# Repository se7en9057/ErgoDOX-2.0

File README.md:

# ErgoDOX-2.0
 
(Circuit design based on the Let's Split PCB)<br />
An update to a classic. <br />
-more switch compatibility<br />
  -MX Alps PG1350<br />
-in switch LED's<br />
-underglow RGB<br />
-Pro Micro each side for individual hand operation<br />
-same PCB layout to ensure compatibility with existing cases. <br />
  -after some consideration in order to bring this board to a more current state using the two controller method i will be adding a second controller to the flip board. meaning there will be some case incompatibility. long term would have an onboard controller which would negate this issue. so R0v1 will not be compatible with existing standard cases with out modification or standoffs.<br />

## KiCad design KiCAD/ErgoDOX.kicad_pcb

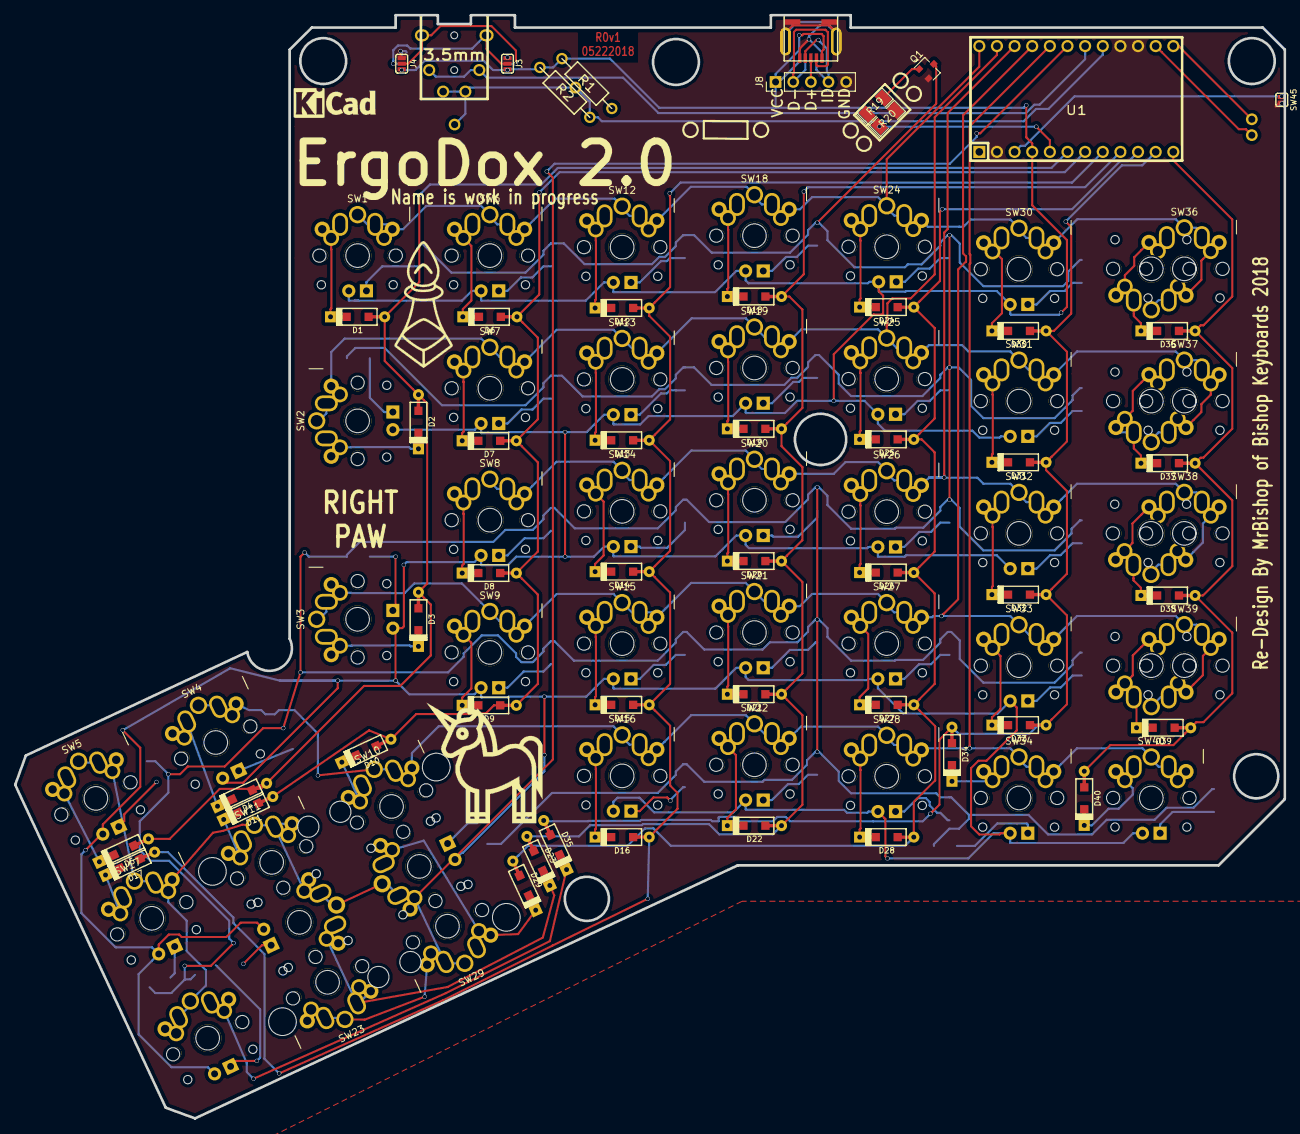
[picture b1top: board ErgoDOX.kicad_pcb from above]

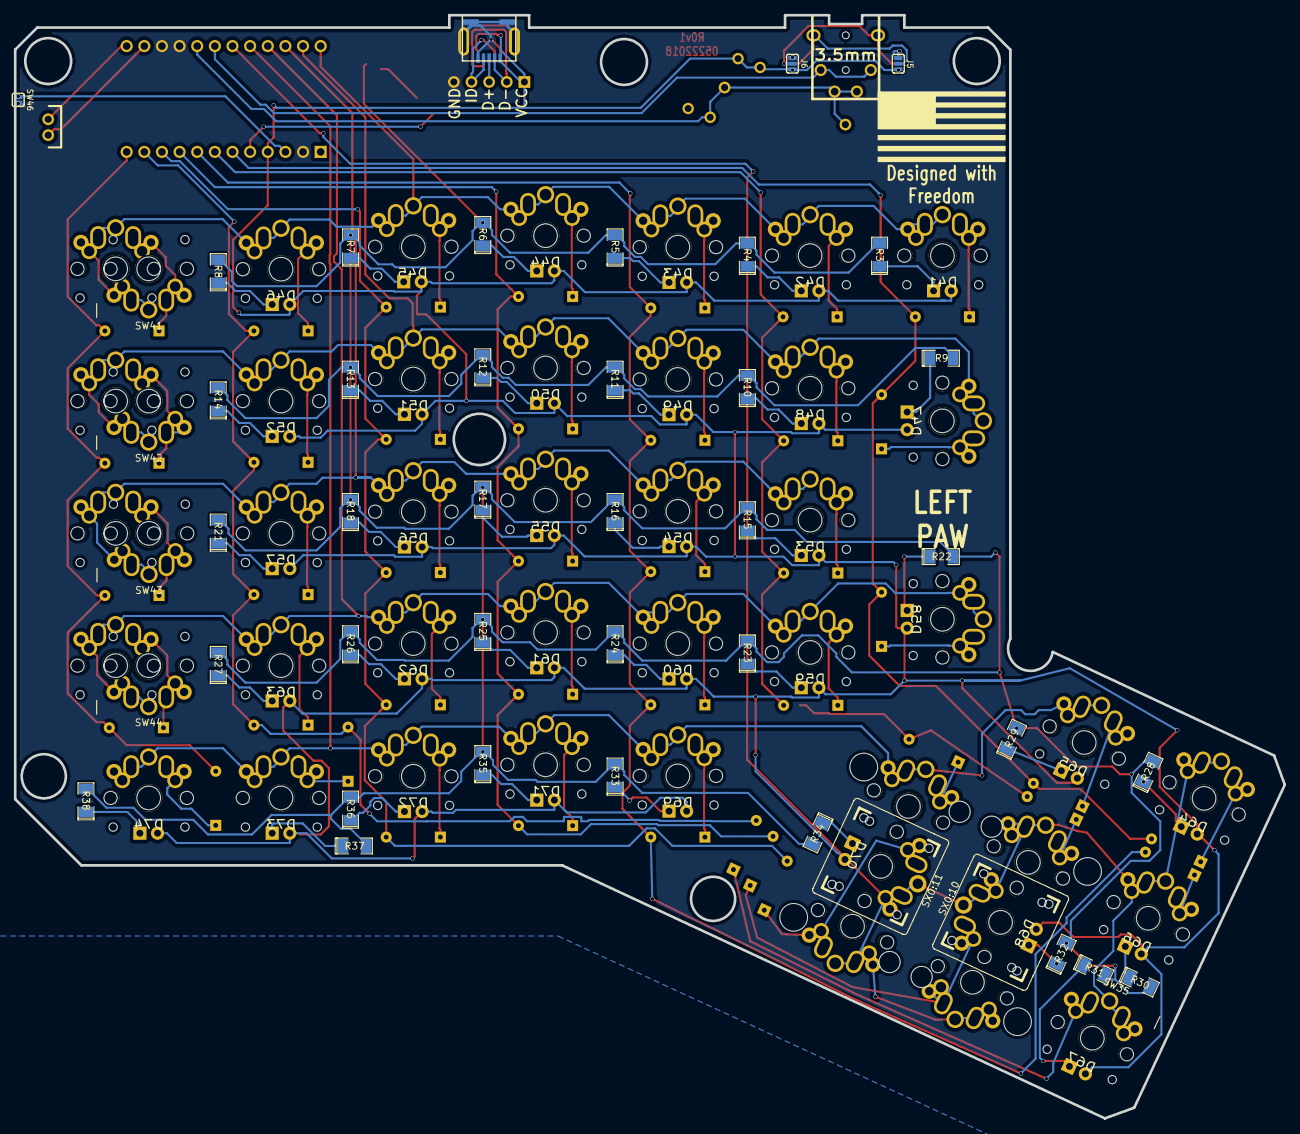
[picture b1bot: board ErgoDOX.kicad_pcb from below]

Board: 2 copper layers, 182.8 x 158.9 mm, 174 parts (45 on the bottom side), 102 nets.

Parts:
D1, D2, D3, D4, D5, D6, D7, D8, D9, D10, D11, D12, D13, D14, D15, D16, D17, D18, D19, D20, D21, D22, D23, D24, D25, D26, D27, D28, D29, D30, D31, D32, D33, D34, D35, D36, D37, D38, D39, D40: DIODE; D_SOD123_axial
D41, D42, D43, D44, D45, D46, D47, D48, D49, D50, D51, D52, D53, D54, D55, D56, D57, D58, D59, D60, D61, D62, D63, D64, D65, D66, D67, D68, D69, D70, D71, D72, D73, D74: LED; CHERRY_MX_LED
J1, J7: USB; USB_miniB_hirose_5S8
J2: 3.5mm; 4pin35mmAudio
J3, J4, J5, J6: JMP; SOLDER_JUMPER_3
J8: Conn_01x05; Pin_Header_Straight_1x05_Pitch2.54mm
Q1: BSS138; SOT-23
R1, R2: 2.2kΩ; RESISTOR
R3, R4, R5, R6, R7, R8, R9, R10, R11, R12, R13, R14, R15, R16, R17, R18, R21, R22, R23, R24, R25, R26, R27, R28, R29, R30, R31, R32, R33, R34, R35, R36, R37, R38: 470; SMD-1206_Pol
R19, R20: 100; SMD-1206_Pol
SW1, SW2, SW3, SW4, SW5, SW6, SW7, SW8, SW9, SW10, SW11, SW12, SW13, SW14, SW15, SW16, SW17, SW18, SW19, SW20, SW21, SW22, SW23, SW24, SW25, SW26, SW27, SW28, SW29, SW30, SW31, SW32, SW33, SW34, SW35, SW36, SW37, SW38, SW39, SW40, SW41, SW42, SW43, SW44: SWITCH_PUSH; MX-ALPs-PG1350-FLIP
SW45, SW46: SWITCH_PUSH; SOLDER_JUMPER_2
SX0:10: SX0:3; MX-ALPs-PG1350-FLIP-2U
SX0:11: SX0:2; MX-ALPs-PG1350-FLIP-2U
U1: ProMicro; ARDUINO_PRO_MICRO
W1, W2, W3, W4: TEST_1P; PIN_1

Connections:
/COL0: D36.2, D37.2, D38.2, D39.2, D40.2, U1.12
/COL1: D30.2, D31.2, D32.2, D33.2, D34.2, D35.2, U1.11
/COL2: D24.2, D25.2, D26.2, D27.2, D28.2, D29.2, U1.10
/COL3: D18.2, D19.2, D20.2, D21.2, D22.2, D23.2, U1.9
/COL4: D12.2, D13.2, D14.2, D15.2, D16.2, D17.2, U1.8
/COL5: D6.2, D7.2, D8.2, D9.2, D10.2, D11.2, U1.7
/COL6: D1.2, D2.2, D3.2, D4.2, D5.2, U1.6
/D+: J1.3, J7.3, J8.3
/D-: J1.2, J7.2, J8.2
/DATA: J2.2, J2.6, U1.18
/ID: J1.4, J7.4, J8.4
/ROW0: SW5.1, SW11.1, SW17.1, SW23.1, SW29.1, SW35.1, SX0:10.1, SX0:11.1, U1.19
/ROW1: SW4.1, SW10.1, SW16.1, SW22.1, SW28.1, SW34.1, SW40.1, U1.20
/ROW2: SW3.1, SW9.1, SW15.1, SW21.1, SW27.1, SW33.1, SW39.1, SW44.1, U1.21
/ROW3: SW8.1, SW14.1, SW20.1, SW26.1, SW32.1, SW38.1, SW43.1, U1.22
/ROW4: SW2.1, SW7.1, SW13.1, SW19.1, SW25.1, SW31.1, SW37.1, SW42.1, U1.23
/ROW5: SW1.1, SW6.1, SW12.1, SW18.1, SW24.1, SW30.1, SW36.1, SW41.1, U1.24
/XTRADATA: J2.3, J2.5, R2.2, U1.17, W1.1, W2.1
/backlight: R19.1, R20.1, U1.5
GND: J1.5, J1.6, J3.1, J4.1, J5.1, J6.1, J7.5, J7.6, J8.5, Q1.2, R20.2, SW45.2, SW46.2, U1.2, U1.15, U1.16
unnamed: D1.1, SW1.2
unnamed: D2.1, SW2.2
unnamed: D3.1, SW3.2
unnamed: D4.1, SW4.2
unnamed: D5.1, SW5.2
unnamed: D6.1, SW6.2
unnamed: D7.1, SW7.2
unnamed: D8.1, SW8.2
unnamed: D9.1, SW9.2
unnamed: D10.1, SW10.2
unnamed: D11.1, SW11.2
unnamed: D12.1, SW12.2
unnamed: D13.1, SW13.2
unnamed: D14.1, SW14.2
unnamed: D15.1, SW15.2
unnamed: D16.1, SW16.2
unnamed: D17.1, SW17.2
unnamed: D18.1, SW18.2
unnamed: D19.1, SW19.2
unnamed: D20.1, SW20.2
unnamed: D21.1, SW21.2
unnamed: D22.1, SW22.2
unnamed: D23.1, SW23.2, SX0:10.2
unnamed: D24.1, SW24.2
unnamed: D25.1, SW25.2
unnamed: D26.1, SW26.2
unnamed: D27.1, SW27.2
unnamed: D28.1, SW28.2
unnamed: D29.1, SW29.2, SX0:11.2
unnamed: D30.1, SW30.2
unnamed: D31.1, SW31.2
unnamed: D32.1, SW32.2
unnamed: D33.1, SW33.2
unnamed: D34.1, SW34.2
unnamed: D35.1, SW35.2
unnamed: D36.1, SW36.2, SW41.2
unnamed: D37.1, SW37.2, SW42.2
unnamed: D38.1, SW38.2, SW43.2
unnamed: D39.1, SW39.2, SW44.2
unnamed: D40.1, SW40.2
unnamed: D41.2, R3.1
unnamed: D42.2, R4.1
unnamed: D43.2, R5.1
unnamed: D44.2, R6.1
unnamed: D45.2, R7.1
unnamed: D46.2, R8.1
unnamed: D47.2, R9.1
unnamed: D48.2, R10.1
unnamed: D49.2, R11.1
unnamed: D50.2, R12.1
unnamed: D51.2, R13.1
unnamed: D52.2, R14.1
unnamed: D53.2, R15.1
unnamed: D54.2, R16.1
unnamed: D55.2, R17.1
unnamed: D56.2, R18.1
unnamed: D57.2, R21.1
unnamed: D58.2, R22.1
unnamed: D59.2, R23.1
unnamed: D60.2, R24.1
unnamed: D61.2, R25.1
unnamed: D62.2, R26.1
unnamed: D63.2, R27.1
unnamed: D64.2, R28.1
unnamed: D65.2, R29.1
unnamed: D66.2, R30.1
unnamed: D67.2, R31.1
unnamed: D68.2, R32.1
unnamed: D69.2, R33.1
unnamed: D70.2, R34.1
unnamed: D71.2, R35.1
unnamed: D72.2, R36.1
unnamed: D73.2, R37.1
unnamed: D74.2, R38.1
unnamed: J2.1, J3.2, J5.2
unnamed: J2.4, J4.2, J6.2
unnamed: Q1.1, R19.2
unnamed: Q1.3, R3.2, R4.2, R5.2, R6.2, R7.2, R8.2, R9.2, R10.2, R11.2, R12.2, R13.2, R14.2, R15.2, R16.2, R17.2, R18.2, R21.2, R22.2, R23.2, R24.2, R25.2, R26.2, R27.2, R28.2, R29.2, R30.2, R31.2, R32.2, R33.2, R34.2, R35.2, R36.2, R37.2, R38.2
unnamed: SW45.1, SW46.1, U1.3
unnamed: U1.13, W3.1
unnamed: U1.14, W4.1
VCC: D41.1, D42.1, D43.1, D44.1, D45.1, D46.1, D47.1, D48.1, D49.1, D50.1, D51.1, D52.1, D53.1, D54.1, D55.1, D56.1, D57.1, D58.1, D59.1, D60.1, D61.1, D62.1, D63.1, D64.1, D65.1, D66.1, D67.1, D68.1, D69.1, D70.1, D71.1, D72.1, D73.1, D74.1, J1.1, J3.3, J4.3, J5.3, J6.3, J7.1, J8.1, R1.1, R2.1, U1.4

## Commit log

2018-05-22 component placement
2018-05-22 removed old traces
2018-05-23 component placement circuit mod
    replicated the Let's split cirucit design to this project. finilized placement of the initial components
2018-05-23 took a picture
    everyone likes pictures
2018-05-23 autosave
2018-05-23 added unicorns
    people love unicorns
2018-05-23 fixed switch placement and begun traces
2018-05-23 initial traces complete
    dont judge me on the thumb section i'm not crazy about how weird the wire traces are either.
2018-05-23 moved stuff around
2018-05-28 added in switch LED
2018-05-28 led's placed
2018-05-28 led circuit and placement
    finisehd placing led components and traces
2018-05-28 updated picture
2018-05-28 tweaks
